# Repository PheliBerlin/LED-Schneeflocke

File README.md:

# LED-Schneeflocke

Eine leuchtende LED Schneeflocke für den Schreibtisch

Gesteuert wird alles mit einen ATtiny84, der mit zwei Shiftregistern die 30 LED schaltet.

Als Fuß habe ich ein Stück Holz vom Olivenbaum genommen.

Da es zum Anschluß an den USB- Anschluß gedacht war, sollte es auch nicht zu viel Strom ziehen. Obwohl ich auf keine Optimierungen im Stromverbrauch geachtet habe, ist der Stromverbrauch auch bei allen 30 leuchtenden LED nur gering.

Die Veröffentlichung erfolgt hier unter GNU General Public License Version 3.

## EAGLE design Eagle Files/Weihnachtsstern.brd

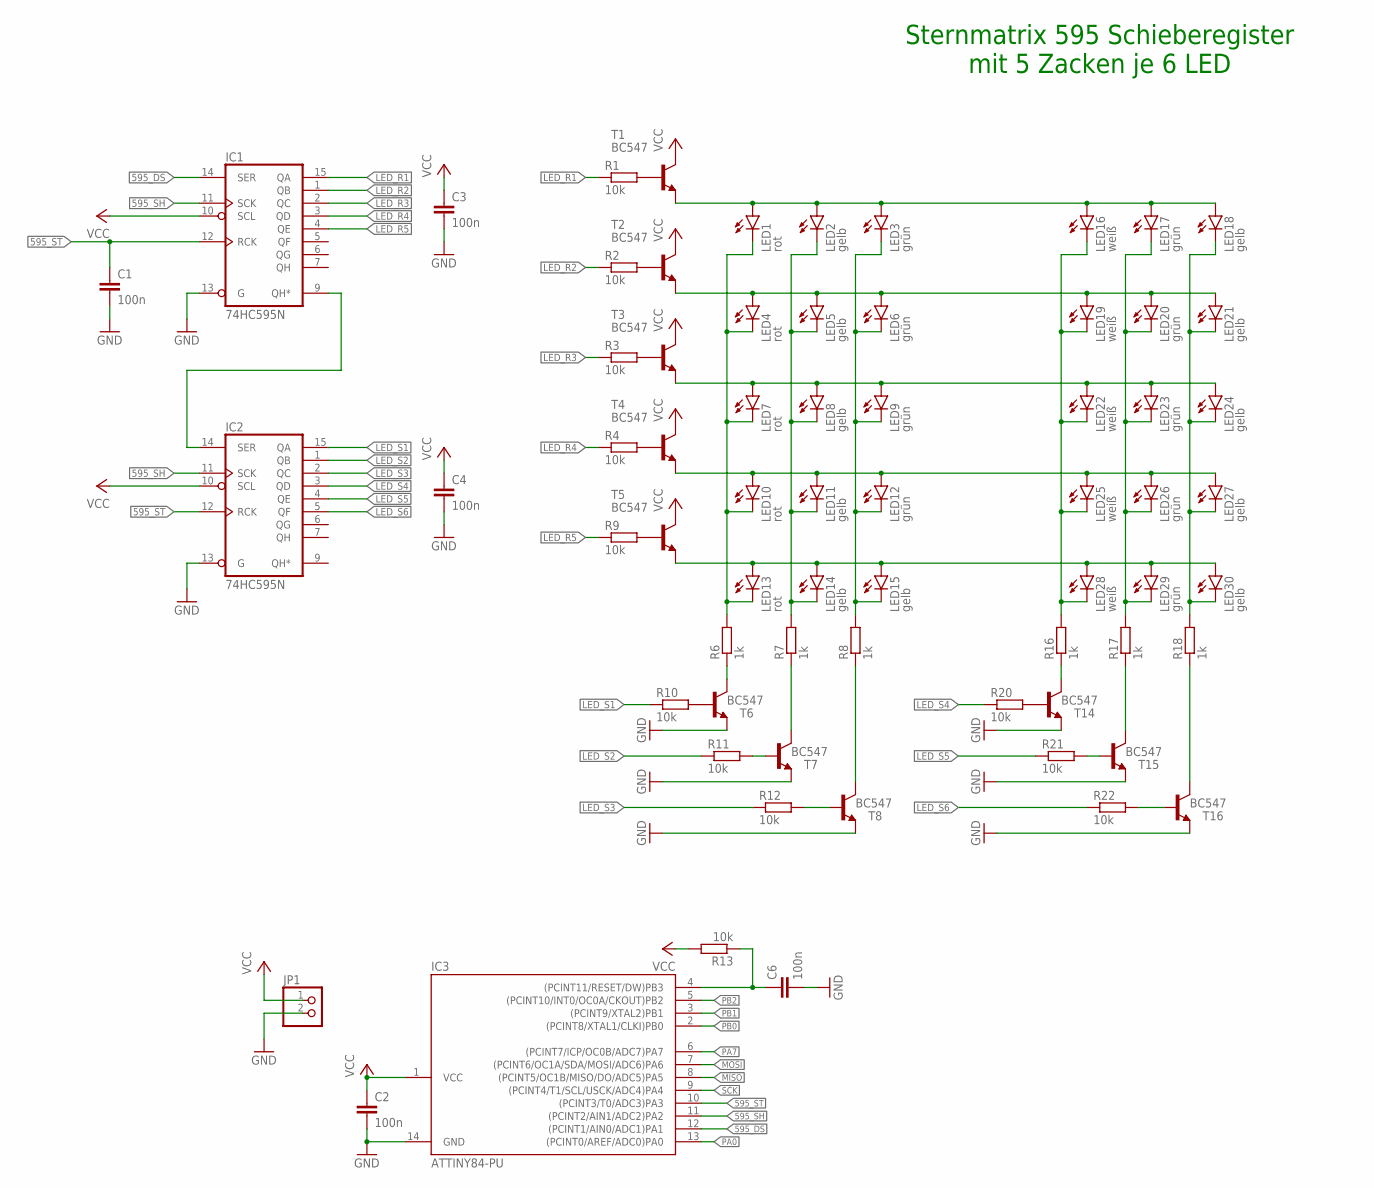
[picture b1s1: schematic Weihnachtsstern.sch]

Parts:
C1, C2, C3, C4, C6: 100n; C025-024X044
IC1, IC2: 74HC595N; DIL16
IC3: ATTINY84-PU; DIL14
JP1: PINHD-1X2; 1X02
LED1, LED4, LED7, LED10, LED13: rot; LED3MM
LED2, LED5, LED8, LED11, LED14, LED15, LED18, LED21, LED24, LED27, LED30: gelb; LED3MM
LED3, LED6, LED9, LED12, LED17, LED20, LED23, LED26, LED29: grün; LED3MM
LED16, LED19, LED22, LED25, LED28: weiß; LED3MM
R1, R2, R3, R4, R9, R10, R11, R12, R13, R20, R21, R22: 10k; 0204/5
R6, R7, R8, R16, R17, R18: 1k; 0204/5
T1, T2, T3, T4, T5, T6, T7, T8, T14, T15, T16: BC547; TO92

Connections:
595_DS: IC1.14 (SER), IC3.12 ((PCINT1/AIN0/ADC1)PA1)
595_SH: IC1.11 (SCK), IC2.11 (SCK), IC3.11 ((PCINT2/AIN1/ADC2)PA2)
595_ST: C1.1, IC1.12 (RCK), IC2.12 (RCK), IC3.10 ((PCINT3/T0/ADC3)PA3)
GND: C1.2, C2.2, C3.2, C4.2, C6.2, IC1.8 (GND), IC1.13 (G), IC2.8 (GND), IC2.13 (G), IC3.14 (GND), JP1.2, T6.1 (E), T7.1 (E), T8.1 (E), T14.1 (E), T15.1 (E), T16.1 (E)
LED_R1: IC1.15 (QA), R1.1
LED_R2: IC1.1 (QB), R2.1
LED_R3: IC1.2 (QC), R3.1
LED_R4: IC1.3 (QD), R4.1
LED_R5: IC1.4 (QE), R9.1
LED_S1: IC2.15 (QA), R10.1
LED_S2: IC2.1 (QB), R11.1
LED_S3: IC2.2 (QC), R12.1
LED_S4: IC2.3 (QD), R20.1
LED_S5: IC2.4 (QE), R21.1
LED_S6: IC2.5 (QF), R22.1
MISO: IC3.8 ((PCINT5/OC1B/MISO/DO/ADC5)PA5)
MOSI: IC3.7 ((PCINT6/OC1A/SDA/MOSI/ADC6)PA6)
unnamed: R7.1, T7.3 (C)
unnamed: R1.2, T1.2 (B)
unnamed: R2.2, T2.2 (B)
unnamed: R3.2, T3.2 (B)
unnamed: R4.2, T4.2 (B)
unnamed: R6.1, T6.3 (C)
unnamed: R8.1, T8.3 (C)
unnamed: R9.2, T5.2 (B)
unnamed: R10.2, T6.2 (B)
unnamed: R11.2, T7.2 (B)
unnamed: R12.2, T8.2 (B)
unnamed: R16.1, T14.3 (C)
unnamed: R18.1, T16.3 (C)
unnamed: R20.2, T14.2 (B)
unnamed: R21.2, T15.2 (B)
unnamed: R22.2, T16.2 (B)
unnamed: R17.1, T15.3 (C)
PA0: IC3.13 ((PCINT0/AREF/ADC0)PA0)
PA7: IC3.6 ((PCINT7/ICP/OC0B/ADC7)PA7)
PB0: IC3.2 ((PCINT8/XTAL1/CLKI)PB0)
PB1: IC3.3 ((PCINT9/XTAL2)PB1)
PB2: IC3.5 ((PCINT10/INT0/OC0A/CKOUT)PB2)
R1: LED1.A, LED2.A, LED3.A, LED16.A, LED17.A, LED18.A, T1.1 (E)
R2: LED4.A, LED5.A, LED6.A, LED19.A, LED20.A, LED21.A, T2.1 (E)
R3: LED7.A, LED8.A, LED9.A, LED22.A, LED23.A, LED24.A, T3.1 (E)
R4: LED10.A, LED11.A, LED12.A, LED25.A, LED26.A, LED27.A, T4.1 (E)
R5: LED13.A, LED14.A, LED15.A, LED28.A, LED29.A, LED30.A, T5.1 (E)
RESET: C6.1, IC3.4 ((PCINT11/RESET/DW)PB3), R13.1
S1: LED1.K (C), LED4.K (C), LED7.K (C), LED10.K (C), LED13.K (C), R6.2
S2: LED2.K (C), LED5.K (C), LED8.K (C), LED11.K (C), LED14.K (C), R7.2
S3: LED3.K (C), LED6.K (C), LED9.K (C), LED12.K (C), LED15.K (C), R8.2
S4: LED16.K (C), LED19.K (C), LED22.K (C), LED25.K (C), LED28.K (C), R16.2
S5: LED17.K (C), LED20.K (C), LED23.K (C), LED26.K (C), LED29.K (C), R17.2
S6: LED18.K (C), LED21.K (C), LED24.K (C), LED27.K (C), LED30.K (C), R18.2
SCK: IC3.9 ((PCINT4/T1/SCL/USCK/ADC4)PA4)
UELAUF: IC1.9 (QH*), IC2.14 (SER)
VCC: C2.1, C3.1, C4.1, IC1.10 (SCL), IC1.16 (VCC), IC2.10 (SCL), IC2.16 (VCC), IC3.1 (VCC), JP1.1, R13.2, T1.3 (C), T2.3 (C), T3.3 (C), T4.3 (C), T5.3 (C)

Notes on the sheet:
Sternmatrix 595 Schieberegister mit 5 Zacken je 6 LED

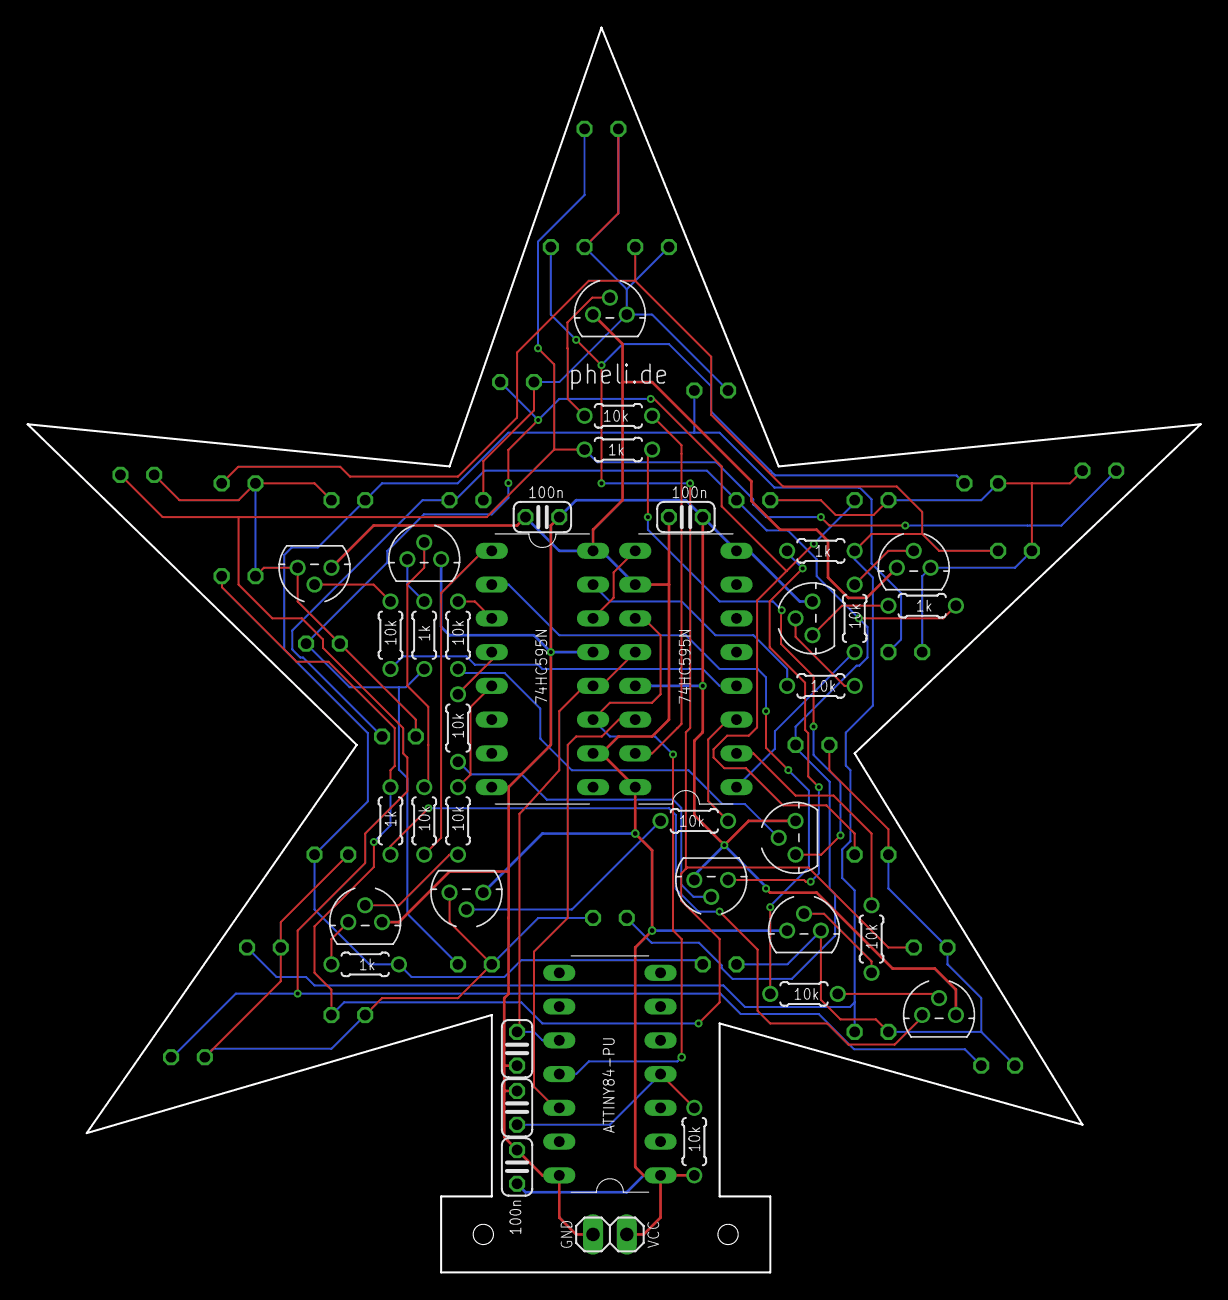
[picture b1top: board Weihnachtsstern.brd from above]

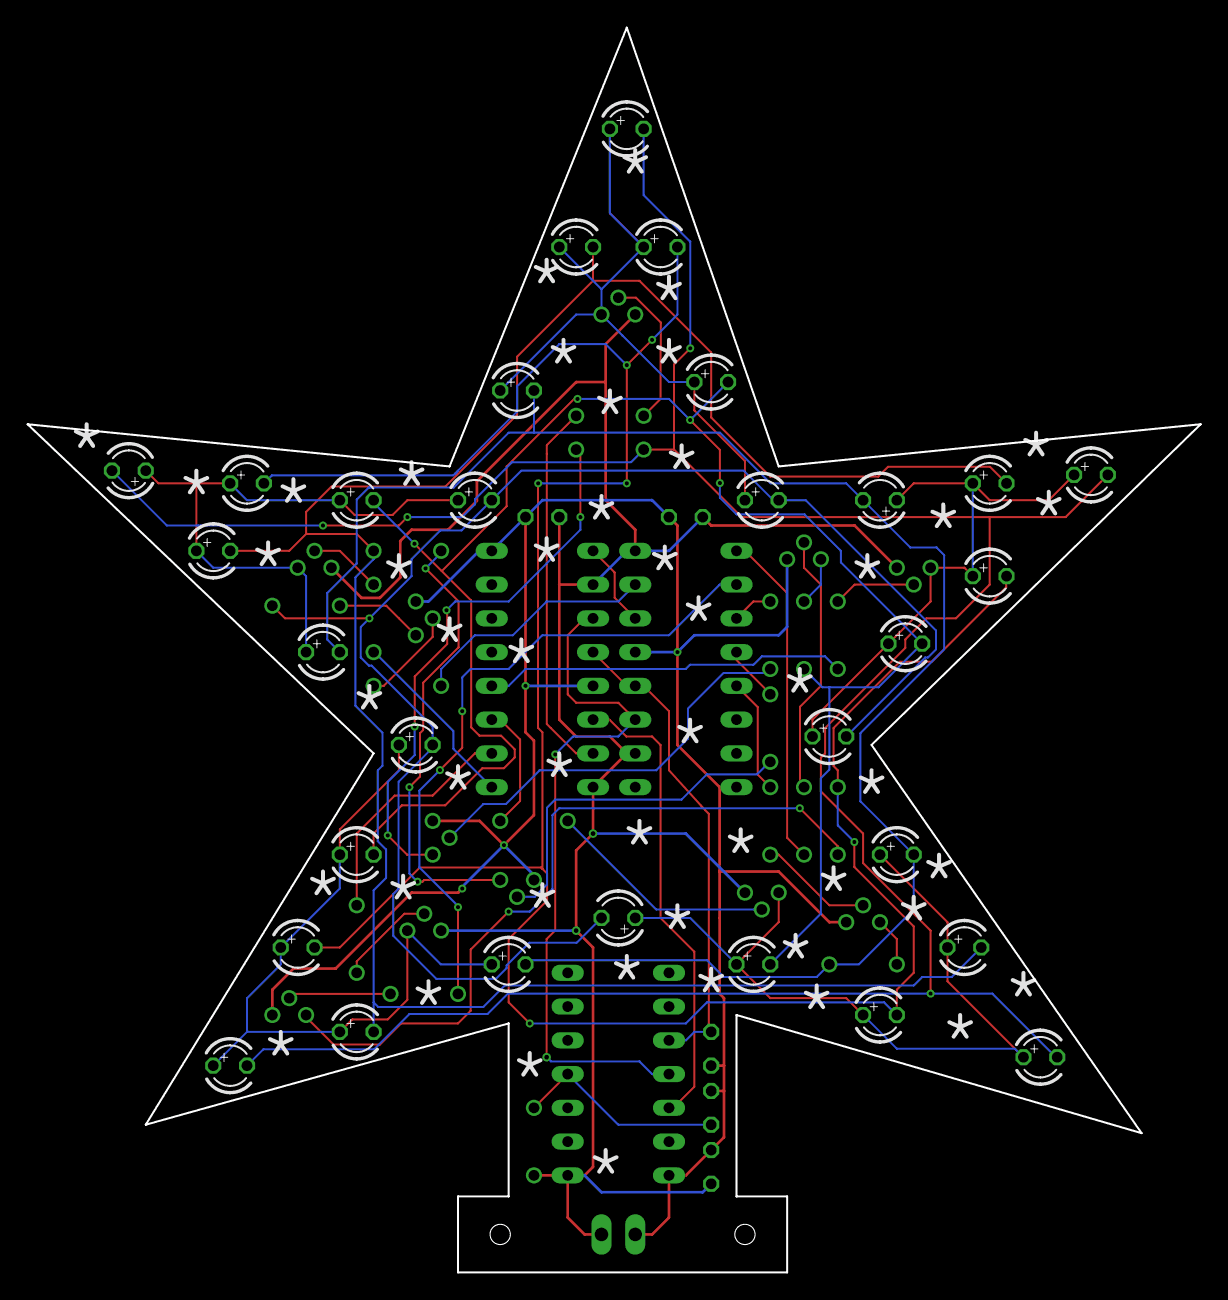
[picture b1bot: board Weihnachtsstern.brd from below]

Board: 2 copper layers, 88.3 x 93.7 mm, 68 parts (30 on the bottom side), 46 nets.

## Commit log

2019-10-06 Weihnachtsflocke
2019-10-06 Gerber Dateien für die Platine
2019-11-25 Beispiel angepasst
2019-11-25 Gerber gelöscht
2019-11-25 Lizenz zugefügt
2019-11-25 Eagle Files zugefügt
2019-11-25 .gitignore angepasst
